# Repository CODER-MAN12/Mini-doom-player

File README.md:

# Mini DOOM Game Console 🕹️💀

A portable, custom-designed handheld gaming console built to run a port of **DOOM**, powered by an **ESP32-S3** microcontroller and an 8-button custom mechanical keypad.

---

## 🚀 Project Overview

This repository contains the hardware design files, schematics, and Bill of Materials (BOM) for a custom-fabricated circuit board designed for a mini retro gaming console. 

> **Note on Firmware:** The firmware for this project (running the DOOM port and handling input/display rendering) is **not** hosted or developed in this specific repository. This repo focuses strictly on the hardware engineering, PCB layout, and physical components.

---

## 🛠️ Hardware Specifications

* **Microcontroller:** ESP32-S3-WROOM-2 (Dual-core Xtensa 32-bit LX7, Wi-Fi & BLE)
* **Input Array:** 8× Mechanical Push Switches / Tactile Buttons
* **Power Management:** USB-C powered via a 16-pin receptacle, stepped down via an LD1117S33TR 3.3V LDO regulator with proper 5.1kΩ CC pull-down resistors.
* **Display Interface:** High-resolution display module support.
* **Board Fabrication:** Custom 2-layer PCB designed in KiCad, fabricated via PCBWay.

---

## 📂 Repository Structure

```text
├── Pdb design/              # KiCad project files, schematics, and PCB layouts
│   └── game boy fake/       # Main hardware project files & 3D models (.step)
├── Images and videos/       # Prototype photos, build logs, and testing clips
├── BOM.csv                  # Complete Bill of Materials with supplier links and costs
└── README.md                # Project documentation

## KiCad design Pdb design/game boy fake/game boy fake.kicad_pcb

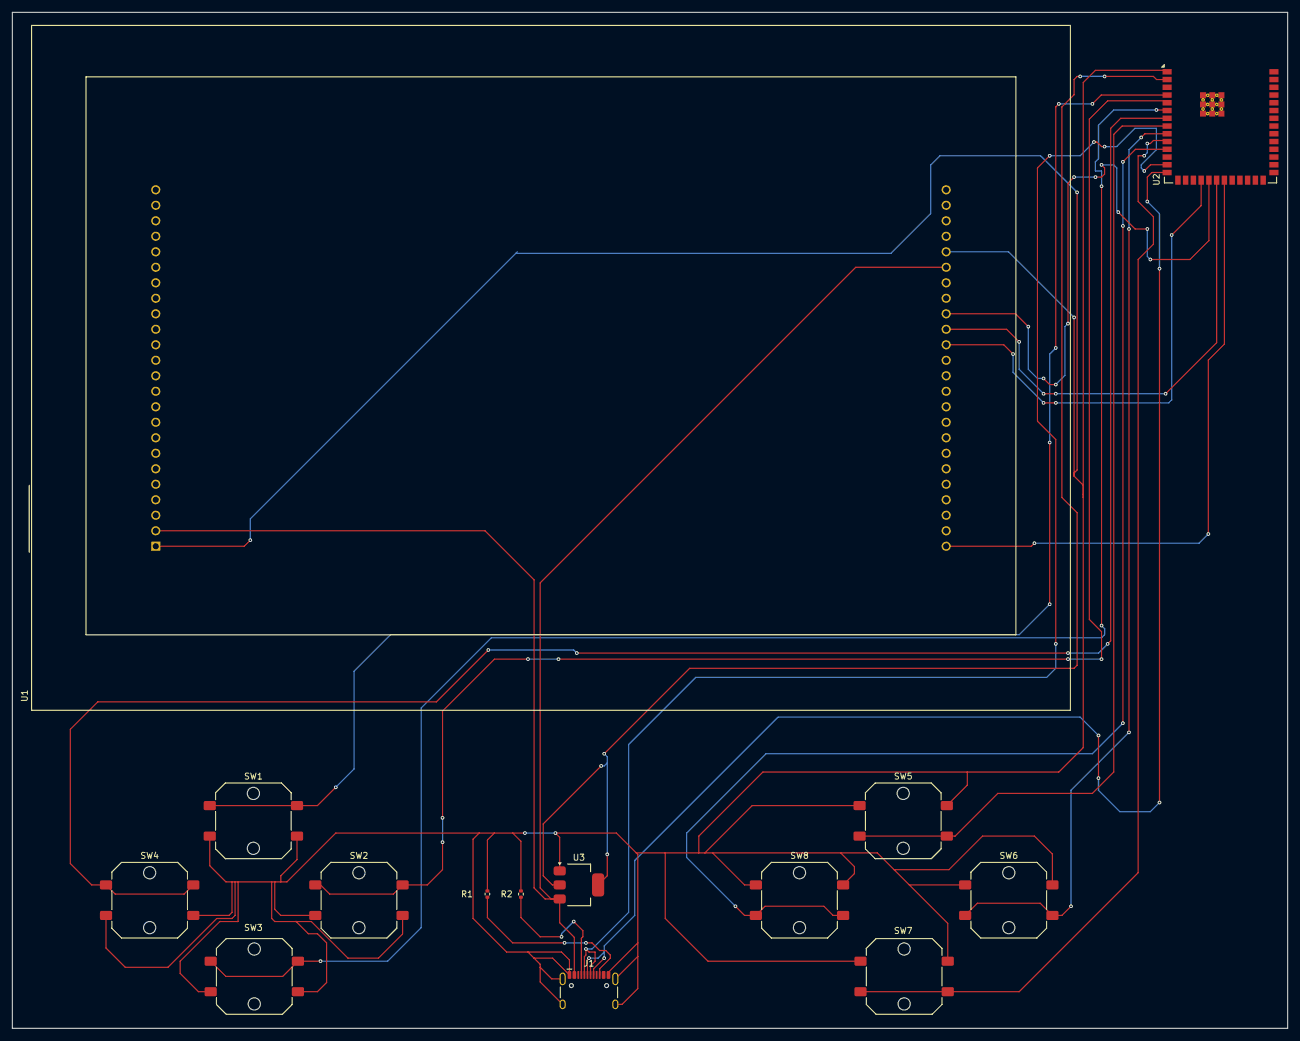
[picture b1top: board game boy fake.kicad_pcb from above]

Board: 2 copper layers, 209.0 x 166.5 mm, 14 parts (0 on the bottom side), 19 nets.

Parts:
J1: USB_C_Receptacle_USB2.0_16P; USB_C_Receptacle_HCTL_HC-TYPE-C-16P-01A
R1, R2: 5.1k; R_0402_1005Metric
SW1, SW2, SW3, SW4, SW5, SW6, SW7, SW8: SW_Push; SW_Push_1P1T_NO_CK_PTS125Sx43PSMTR
U1: EA_eDIPTFT70-A; EA_eDIPTFT70-XXX
U2: ESP32-S3-WROOM-2
U3: LD1117S33TR_SOT223; SOT-223-3_TabPin2

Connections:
unnamed: J1.A5 (CC1), R2.1
unnamed: J1.B5 (CC2), R1.1
unnamed: J1.A1 (GND), J1.A12 (GND), J1.B1 (GND), J1.B12 (GND), J1.SH (SHIELD), R1.2, R2.2, SW1.2, SW2.2, SW3.2, SW4.2, SW5.1, SW6.1, SW7.1, SW8.1, U1.1 (GND), U1.29 (GND), U2.1 (GND), U2.40 (GND), U2.41 (GND), U3.1 (GND)
unnamed: U1.48 (IN8/MI1), U2.21 (IO13)
unnamed: U1.33 (OUT1/MO8), U2.19 (IO11)
unnamed: U1.34 (OUT2/MO7), U2.20 (IO12)
unnamed: U1.35 (OUT3/MO6), U2.18 (IO10)
unnamed: U2.2 (3V3), U3.2 (VO)
unnamed: SW1.1, U2.4 (IO4)
unnamed: SW2.1, U2.5 (IO5)
unnamed: SW3.1, U2.6 (IO6)
unnamed: SW4.1, U2.7 (IO7)
unnamed: SW5.2, U2.8 (IO15)
unnamed: SW6.2, U2.9 (IO16)
unnamed: SW7.2, U2.10 (IO17)
unnamed: SW8.2, U2.11 (IO18)
unnamed: J1.A6 (D+), J1.B6 (D+), U2.14 (USB_D+/IO20)
unnamed: J1.A7 (D-), J1.B7 (D-), U2.13 (USB_D-/IO19)
unnamed: J1.A4 (VBUS), J1.A9 (VBUS), J1.B4 (VBUS), J1.B9 (VBUS), U1.2 (VDD), U1.30 (VDD), U3.3 (VI)

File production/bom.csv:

Designator,Footprint,Quantity,Value,LCSC Part #
J1,USB_C_Receptacle_HCTL_HC-TYPE-C-16P-01A,1,USB_C_Receptacle_USB2.0_16P,
"R1, R2",0402,2,5.1k,
"SW1, SW2, SW3, SW4, SW5, SW6, SW7, SW8",SW_Push_1P1T_NO_CK_PTS125Sx43PSMTR,8,SW_Push,
U1,EA_eDIPTFT70-XXX,1,EA_eDIPTFT70-A,
U2,ESP32-S3-WROOM-2,1,ESP32-S3-WROOM-2,
U3,SOT-223-3_TabPin2,1,LD1117S33TR_SOT223,
